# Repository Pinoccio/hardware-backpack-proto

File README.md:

proto-hardware-reference
===========================

Contained are the schematics, board layout, data sheets, and BOM for the Pinoccio proto board.

The board revisions are also marked as tags in the git repository, if you'd like to see a previous version.

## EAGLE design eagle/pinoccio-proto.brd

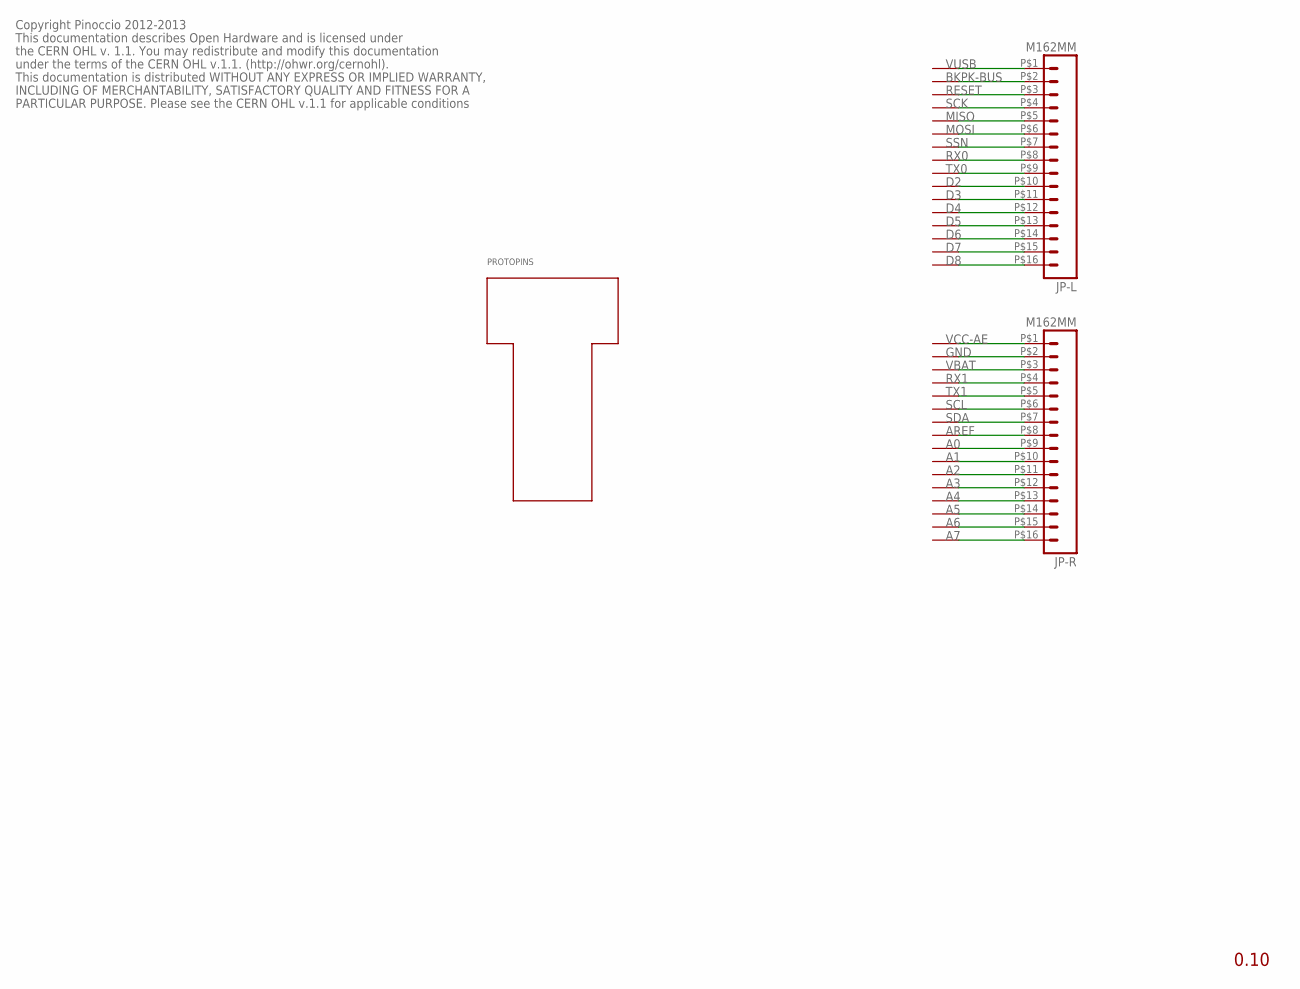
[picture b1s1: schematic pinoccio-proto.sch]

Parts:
JP-L: M162MM; 1X16_2MM
JP-R: M162MM; 1X16_2MM
PROTOPINS: PROTO; 1X1PROTO
U$2, U$3, U$4, U$5, U$6, U$7, U$8, U$9, U$10, U$11, U$12, U$13, U$14, U$15, U$16, U$17, U$18, U$19, U$20, U$21, U$22, U$23, U$24, U$25, U$26, U$27, U$28, U$29, U$30, U$31, U$32, U$33: PAD55-RRECT; PAD-100X55-RRECT

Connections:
A0: JP-R.P$9 (9), U$25.P$1
A1: JP-R.P$10 (10), U$24.P$1
A2: JP-R.P$11 (11), U$23.P$1
A3: JP-R.P$12 (12), U$22.P$1
A4: JP-R.P$13 (13), U$21.P$1
A5: JP-R.P$14 (14), U$20.P$1
A6: JP-R.P$15 (15), U$19.P$1
A7: JP-R.P$16 (16), U$18.P$1
AREF: JP-R.P$8 (8), U$26.P$1
BKPK-BUS: JP-L.P$2 (2), U$15.P$1
D2: JP-L.P$10 (10), U$7.P$1
D3: JP-L.P$11 (11), U$6.P$1
D4: JP-L.P$12 (12), U$5.P$1
D5: JP-L.P$13 (13), U$3.P$1
D6: JP-L.P$14 (14), U$4.P$1
D7: JP-L.P$15 (15), U$2.P$1
D8: JP-L.P$16 (16), U$17.P$1
GND: JP-R.P$2 (2), U$32.P$1
MISO: JP-L.P$5 (5), U$12.P$1
MOSI: JP-L.P$6 (6), U$11.P$1
RESET: JP-L.P$3 (3), U$14.P$1
RX0: JP-L.P$8 (8), U$9.P$1
RX1: JP-R.P$4 (4), U$30.P$1
SCK: JP-L.P$4 (4), U$13.P$1
SCL: JP-R.P$6 (6), U$28.P$1
SDA: JP-R.P$7 (7), U$27.P$1
SSN: JP-L.P$7 (7), U$10.P$1
TX0: JP-L.P$9 (9), U$8.P$1
TX1: JP-R.P$5 (5), U$29.P$1
VBAT: JP-R.P$3 (3), U$31.P$1
VCC-AE: JP-R.P$1 (1), U$33.P$1
VUSB: JP-L.P$1 (1), U$16.P$1

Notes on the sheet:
0.10
Copyright Pinoccio 2012-2013
This documentation describes Open Hardware and is licensed under
the CERN OHL v. 1.1. You may redistribute and modify this documentation
under the terms of the CERN OHL v.1.1. (http://ohwr.org/cernohl).
This documentation is distributed WITHOUT ANY EXPRESS OR IMPLIED WARRANTY,
INCLUDING OF MERCHANTABILITY, SATISFACTORY QUALITY AND FITNESS FOR A
PARTICULAR PURPOSE. Please see the CERN OHL v.1.1 for applicable conditions

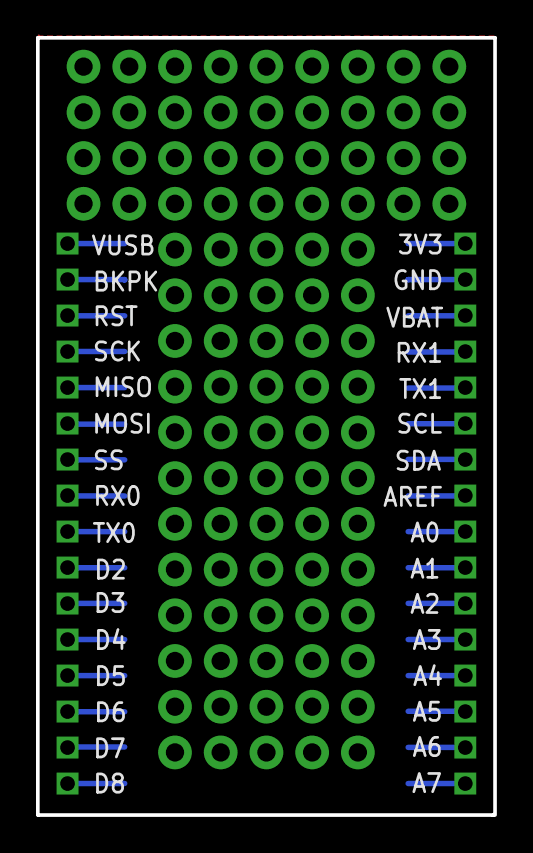
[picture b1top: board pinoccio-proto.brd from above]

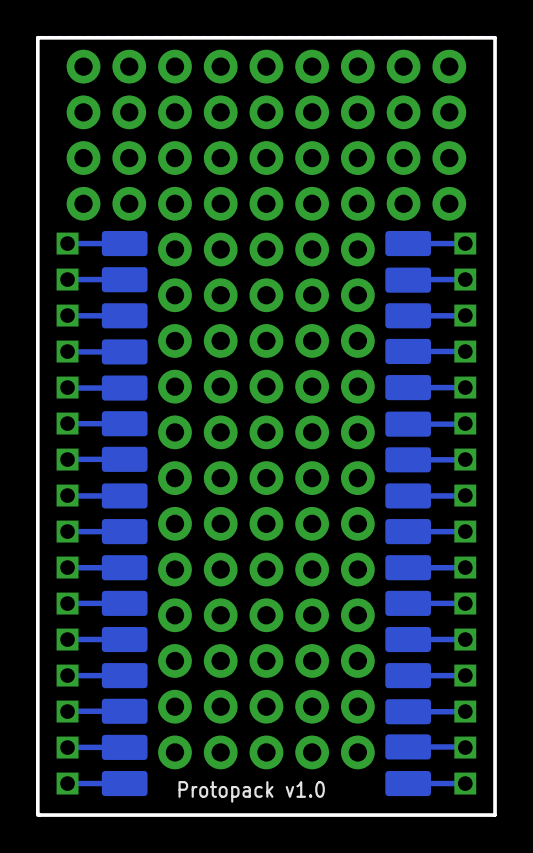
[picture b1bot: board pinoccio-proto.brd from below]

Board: 2 copper layers, 25.4 x 43.2 mm, 35 parts (32 on the bottom side), 32 nets.

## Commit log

2013-01-19 initial import
2013-01-21 Break out ground and power buses to pins
2013-03-13 Update to v0.10, added solderable pads to bottom of board
2014-02-10 version 1.0
2014-02-10 Update chagnes
2014-02-10 Add gitignore
2014-02-19 Add bill of materials file to repo

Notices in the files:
eagle/pinoccio-proto.brd:
Licensed under CERN OHL v.1.1
